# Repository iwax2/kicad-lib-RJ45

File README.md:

# kicad-lib-RJ45

KiCad schematic library and footprint for RJ45 connectors

* 91-RJ01-010 <http://www.aitendo.com/product/10352> and <http://www.aitendo.com/product/10348>
* 7810-8P8C <http://akizukidenshi.com/catalog/g/gC-00159/>

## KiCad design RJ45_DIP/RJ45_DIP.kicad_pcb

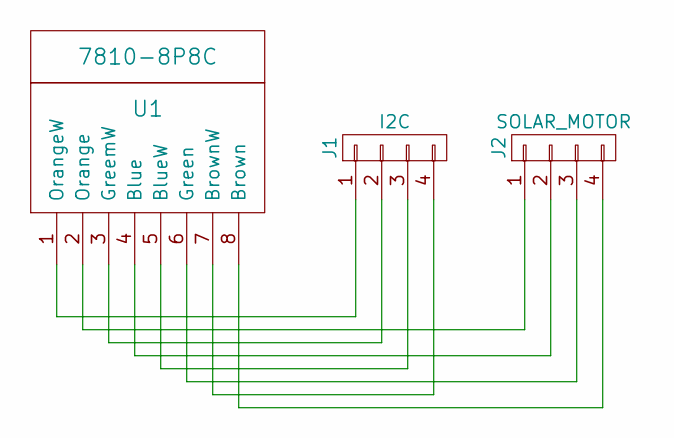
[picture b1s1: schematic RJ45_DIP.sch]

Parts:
J1: I2C; Pin_Header_Straight_1x04_Pitch2.54mm
J2: SOLAR_MOTOR; Pin_Header_Straight_1x04_Pitch2.54mm
U1: 7810-8P8C

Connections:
unnamed: J1.1, U1.1 (OrangeW)
unnamed: J1.2, U1.3 (GreemW)
unnamed: J1.3, U1.5 (BlueW)
unnamed: J1.4, U1.7 (BrownW)
unnamed: J2.1, U1.2 (Orange)
unnamed: J2.2, U1.4 (Blue)
unnamed: J2.3, U1.6 (Green)
unnamed: J2.4, U1.8 (Brown)

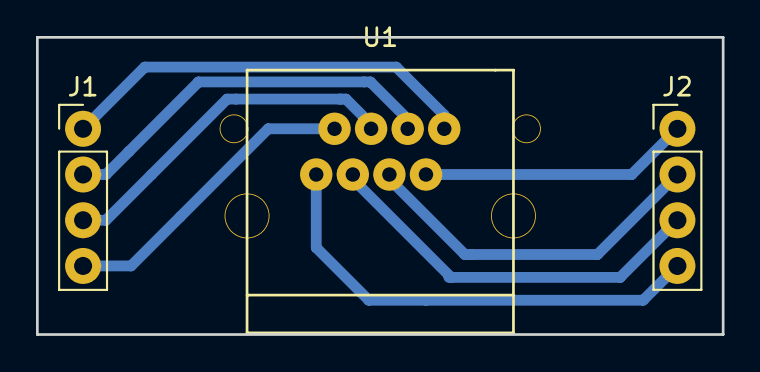
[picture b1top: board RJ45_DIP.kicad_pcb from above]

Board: 2 copper layers, 38.1 x 16.5 mm, 3 parts (0 on the bottom side), 8 nets.

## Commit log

2017-05-31 RJ45 kicad-footprint
2017-07-18 秋月RJ45コネクタ追加
2017-07-18 DIP化基板
2017-08-09 基板を印刷して入ることを確認した（ちょっと固い）
2017-12-22 update 12pin
2018-01-16 ピンが逆だったのを修正
